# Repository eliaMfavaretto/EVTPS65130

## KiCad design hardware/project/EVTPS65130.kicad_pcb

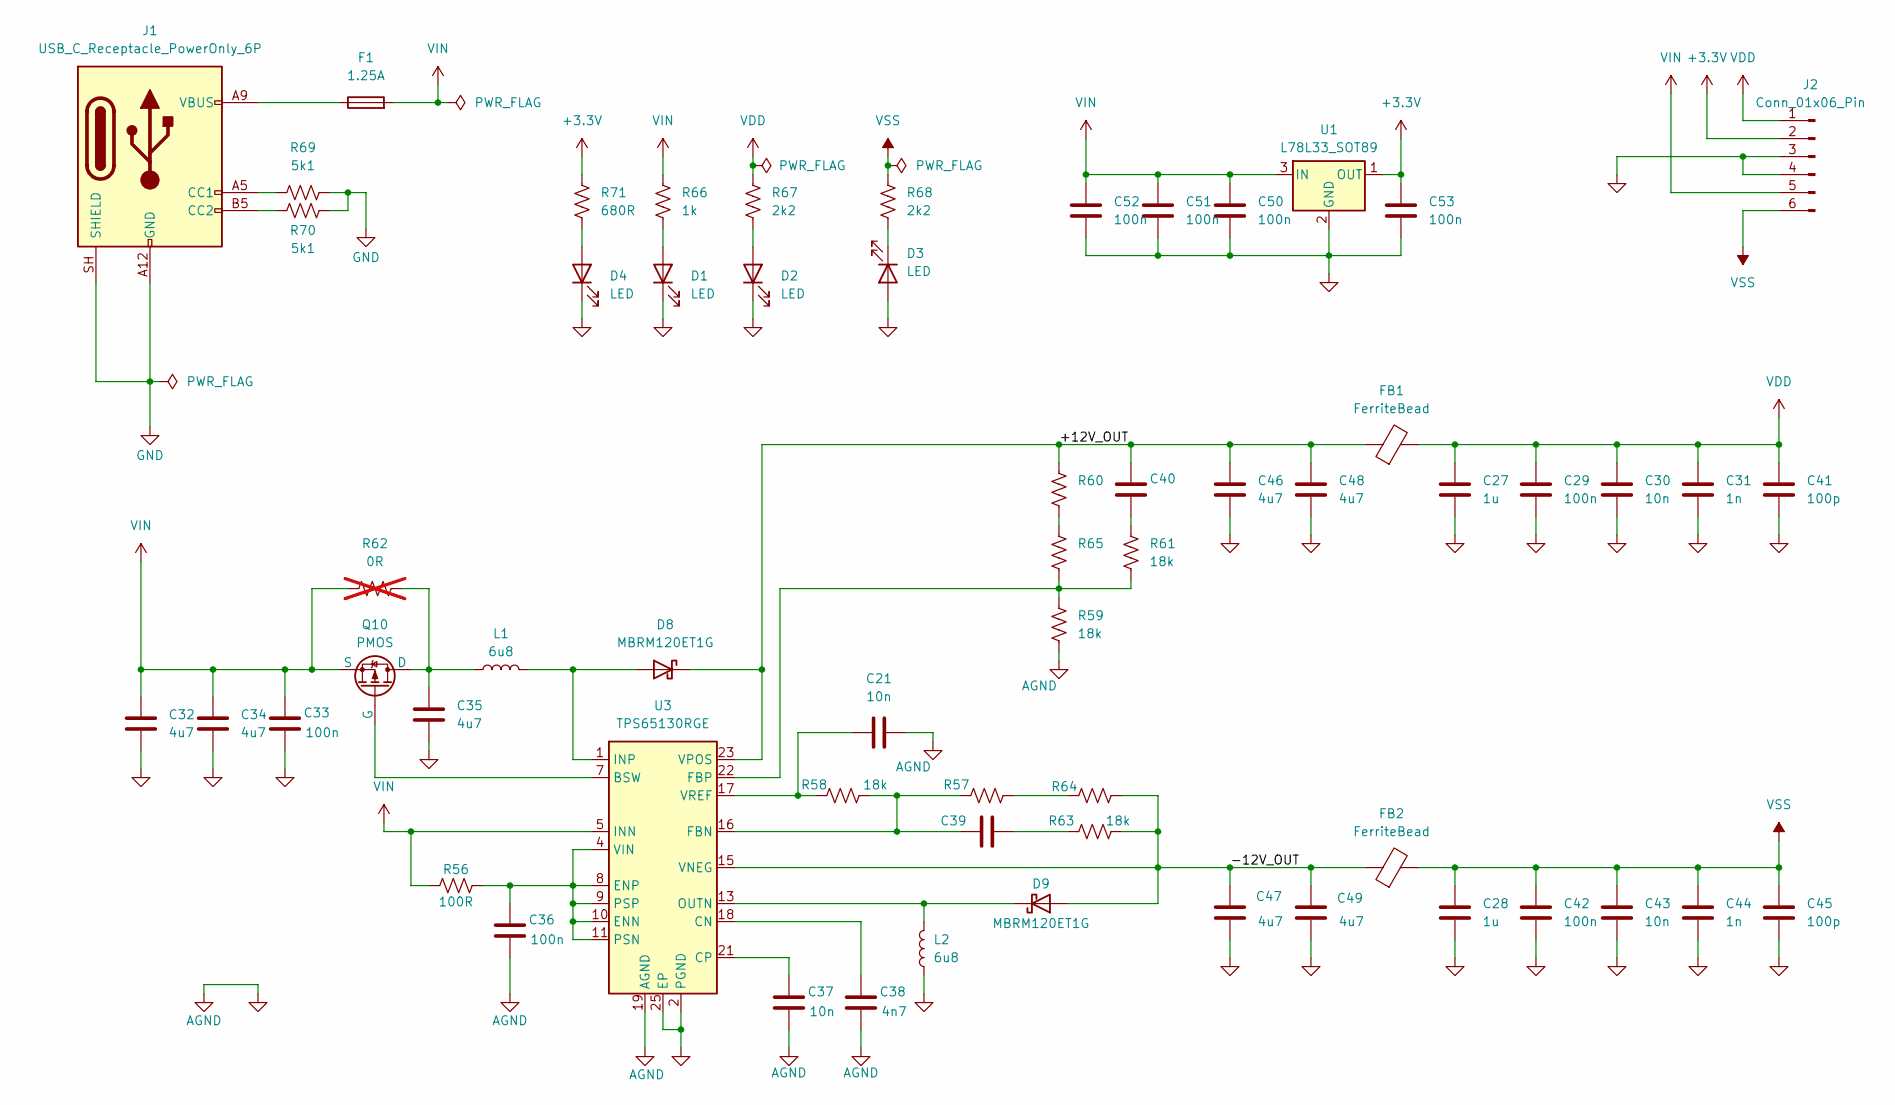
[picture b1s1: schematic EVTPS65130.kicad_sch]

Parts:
C21, C30, C37, C43: 10n; C_0402_1005Metric
C27, C28: 1u; C_0603_1608Metric
C29, C33, C36, C42, C50, C51, C52, C53: 100n; C_0402_1005Metric
C31, C44: 1n; C_0402_1005Metric
C32, C34, C35, C46, C47, C48, C49: 4u7; C_1206_3216Metric
C38: 4n7; C_0402_1005Metric
C39, C40: C_0402_1005Metric
C41, C45: 100p; C_0402_1005Metric
D1, D2, D3, D4: LED; LED_0603_1608Metric
D8, D9: MBRM120ET1G; D_SMA
F1: 1.25A; Fuse_1206_3216Metric_Pad1.42x1.75mm_HandSolder
FB1, FB2: FerriteBead; L_0805_2012Metric
J1: USB_C_Receptacle_PowerOnly_6P; USB_C_Receptacle_GCT_USB4125-xx-x-0190_6P_TopMnt_Horizontal
J2: Conn_01x06_Pin; PinHeader_1x06_P2.54mm_Vertical
L1, L2: 6u8; 74406032068; MPN 74406032068
Q10: PMOS; SOT-23
R56: 100R; R_0402_1005Metric
R57, R60, R64, R65: R_0402_1005Metric
R58, R59, R61, R63: 18k; R_0402_1005Metric
R62: 0R; R_0805_2012Metric; not fitted
R66: 1k; R_0402_1005Metric
R67, R68: 2k2; R_0402_1005Metric
R69, R70: 5k1; R_0402_1005Metric
R71: 680R; R_0402_1005Metric
U1: L78L33_SOT89; SOT-89-3
U3: TPS65130RGE; VQFN-24-1EP_4x4mm_P0.5mm_EP2.45x2.45mm_ThermalVias

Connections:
+3.3V: C53.1, J2.2, R71.2, U1.1 (OUT)
/+12V_OUT: C40.1, C46.1, C48.1, D8.1 (K), FB1.1, R60.2, U3.23 (VPOS)
/-12V_OUT: C47.1, C49.1, D9.2 (A), FB2.1, R63.2, R64.2, U3.15 (VNEG)
AGND: C21.2, C27.2, C28.2, C29.2, C30.2, C31.2, C32.2, C33.2, C34.2, C35.2, C36.2, C37.2, C38.2, C41.2, C42.2, C43.2, C44.2, C45.2, C46.2, C47.2, C48.2, C49.2, C50.2, C51.2, C52.2, C53.2, D1.1 (K), D2.1 (K), D3.2 (A), D4.1 (K), J1.A12 (GND), J1.B12 (GND), J1.SH (SHIELD), J2.3, J2.4, L2.1, R59.2, R69.2, R70.1, U1.2 (GND), U3.2 (PGND), U3.3 (PGND), U3.19 (AGND), U3.25 (EP)
unnamed: C39.2, R63.1
unnamed: C40.2, R61.1
unnamed: D1.2 (A), R66.1
unnamed: D2.2 (A), R67.1
unnamed: D3.1 (K), R68.1
unnamed: D4.2 (A), R71.1
unnamed: D8.2 (A), L1.2, U3.1 (INP), U3.24 (INP)
unnamed: D9.1 (K), L2.2, U3.13 (OUTN), U3.14 (OUTN)
unnamed: F1.1, J1.A9 (VBUS), J1.B9 (VBUS)
unnamed: J1.A5 (CC1), R69.1
unnamed: J1.B5 (CC2), R70.2
unnamed: C35.1, L1.1, Q10.1 (D), R62.2
unnamed: Q10.2 (G), U3.7 (BSW)
unnamed: R57.2, R64.1
unnamed: R60.1, R65.2
unnamed: C38.1, U3.18 (CN)
unnamed: C37.1, U3.21 (CP)
unnamed: C36.1, R56.2, U3.4 (VIN), U3.8 (ENP), U3.9 (PSP), U3.10 (ENN), U3.11 (PSN)
unnamed: C39.1, R57.1, R58.2, U3.16 (FBN)
unnamed: R59.1, R61.2, R65.1, U3.22 (FBP)
unnamed: C21.1, R58.1, U3.17 (VREF)
VDD: C27.1, C29.1, C30.1, C31.1, C41.1, FB1.2, J2.1, R67.2
VIN: C32.1, C33.1, C34.1, C50.1, C51.1, C52.1, F1.2, J2.5, Q10.3 (S), R56.1, R62.1, R66.2, U1.3 (IN), U3.5 (INN), U3.6 (INN)
VSS: C28.1, C42.1, C43.1, C44.1, C45.1, FB2.2, J2.6, R68.2

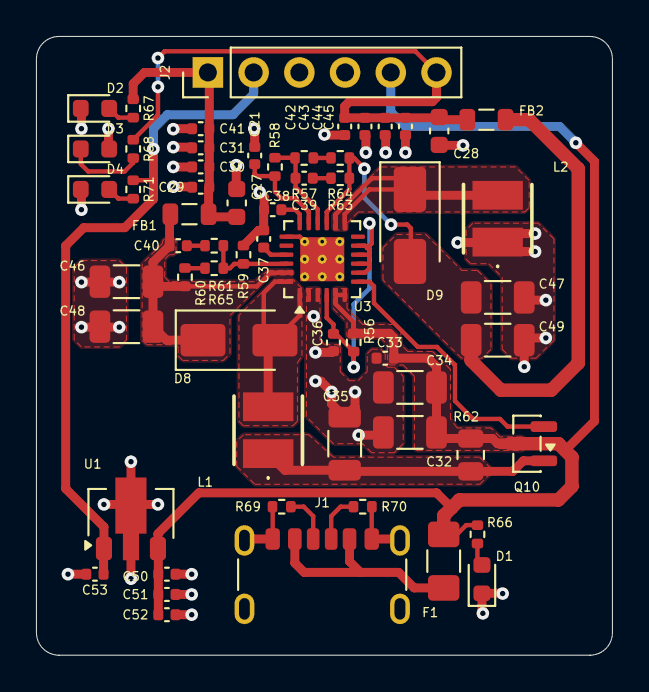
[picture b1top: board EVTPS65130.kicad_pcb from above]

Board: 2 copper layers, 32.0 x 34.4 mm, 60 parts (0 on the bottom side), 28 nets.

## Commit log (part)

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2026-06-21 Added: output filter, values
2026-06-21 Update: added footprint
2026-06-23 Started PCB placement
